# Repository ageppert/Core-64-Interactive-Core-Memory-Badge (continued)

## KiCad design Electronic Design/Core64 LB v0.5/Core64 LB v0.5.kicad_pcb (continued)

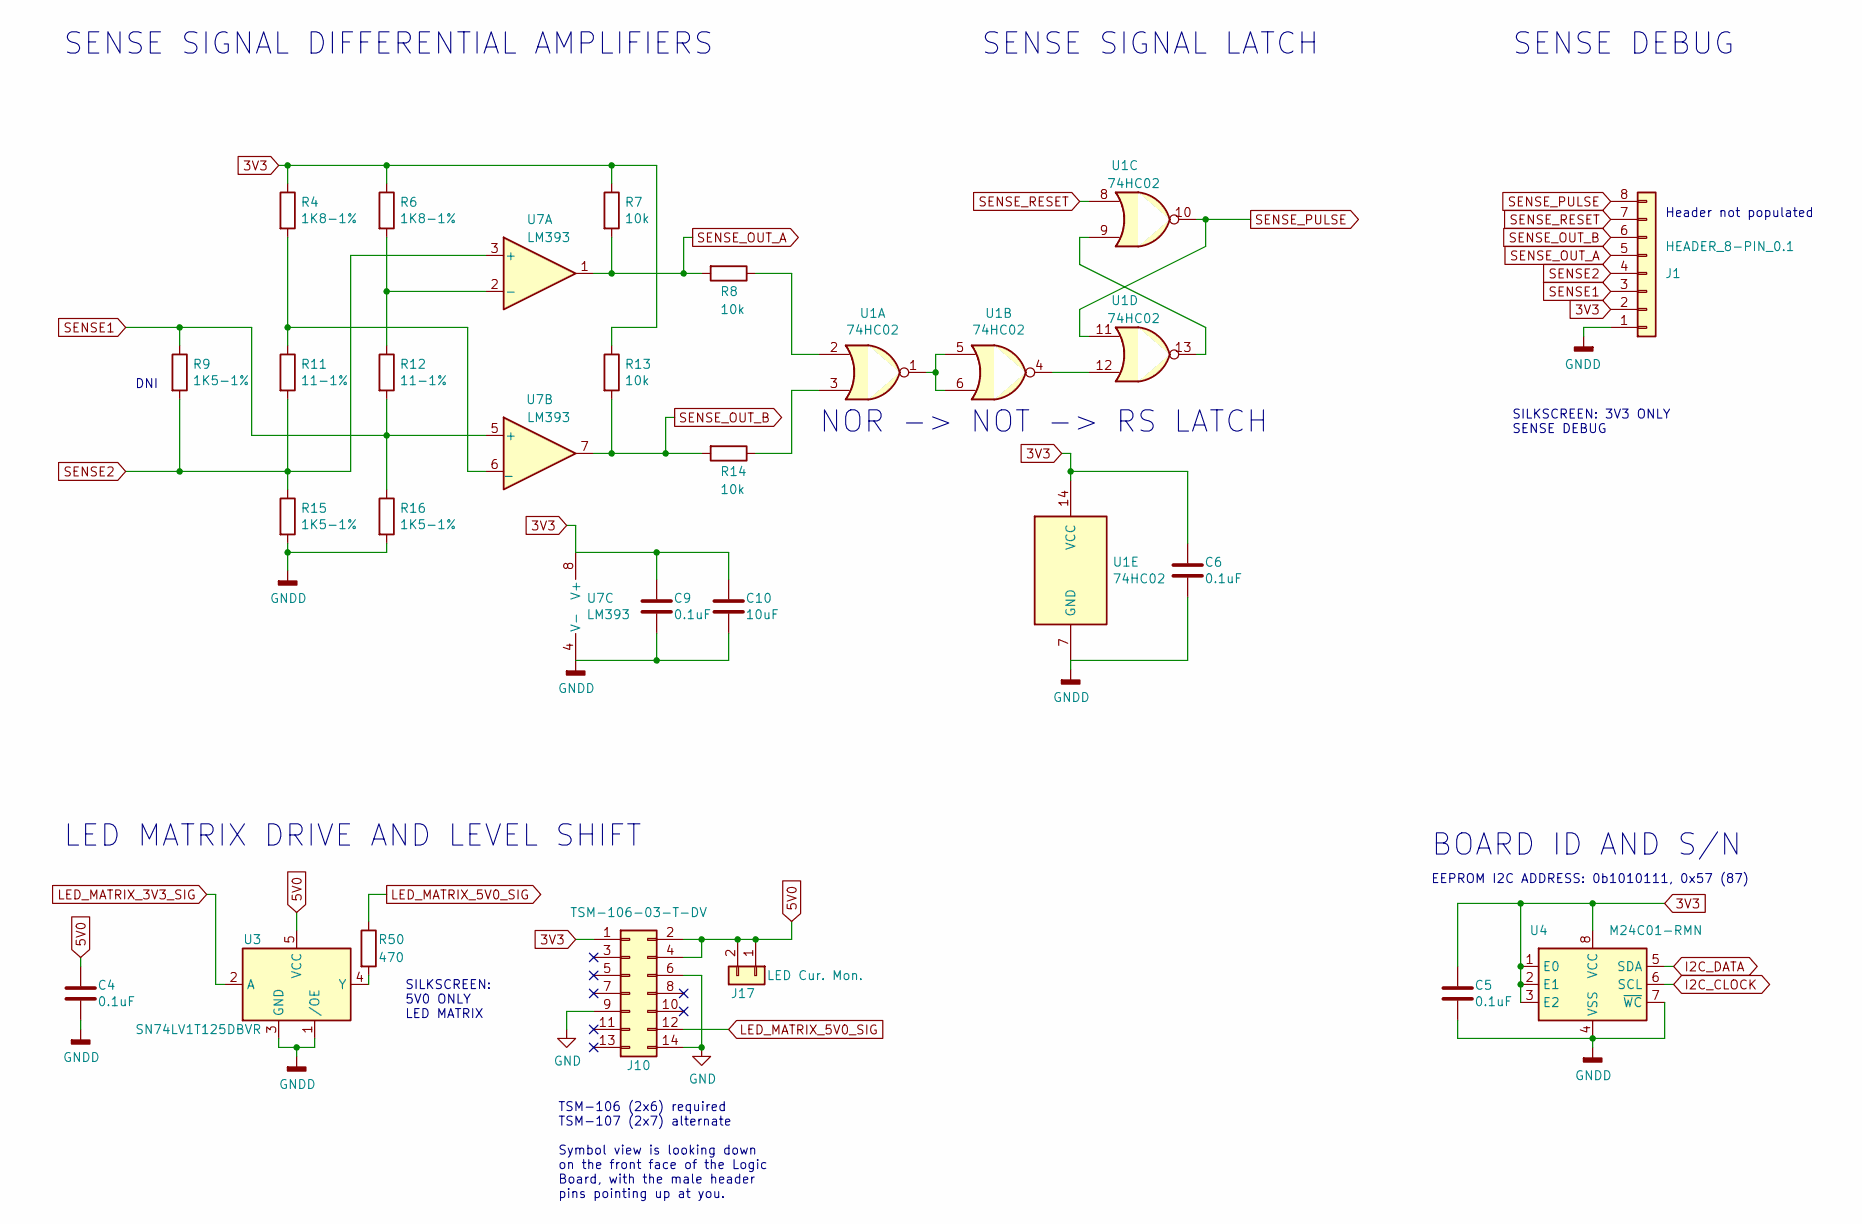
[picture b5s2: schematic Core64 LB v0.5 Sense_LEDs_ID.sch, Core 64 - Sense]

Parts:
C4, C5, C6, C9: 0.1uF; C_0805_2012Metric
C10: 10uF; C_0805_2012Metric
J1: HEADER_8-PIN_0.1; PinSocket_1x08_P2.54mm_Vertical
J10: TSM-106-03-T-DV‎; PinHeader_2x07_P2.54mm_Vertical_SMD_and_TH
J17: LED Cur. Mon.; PinSocket_1x02_P2.54mm_Vertical
R4, R6: 1K8-1%; R_0805_2012Metric
R7, R8, R13, R14: 10k; R_0805_2012Metric
R9, R15, R16: 1K5-1%; R_0805_2012Metric
R11, R12: 11-1%; R_0805_2012Metric
R50: 470; R_0805_2012Metric
U1: 74HC02; SOIC-14_3.9x8.7mm_P1.27mm
U3, U7: LM393; SOIC-8_W3.9mm
U4: M24C01-RMN; SOIC-8_3.9x4.9mm_P1.27mm

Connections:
3V3: C5.1, C6.1, C9.1, C10.1, J1.2, J10.1, R4.1, R6.1, R7.1, R13.1, U1.14 (VCC), U4.1 (E0), U4.2 (E1), U4.3 (E2), U4.8 (VCC), U7.8 (V+); also elsewhere on the board
5V0: C4.1, J10.2, J10.4, J17.1, J17.2, U3.5 (VCC); also elsewhere on the board
I2C_CLOCK: U4.6 (SCL); also elsewhere on the board
I2C_DATA: U4.5 (SDA); also elsewhere on the board
LED_MATRIX_5V0_SIG: J10.12, R50.1; also elsewhere on the board
unnamed: R8.1, U1.2
unnamed: R4.2, R11.1, U7.6 (_)
unnamed: R14.1, U1.3
unnamed: R50.2, U3.4 (Y)
unnamed: U1.1, U1.5, U1.6
unnamed: U1.4, U1.12
unnamed: U1.9, U1.13
SENSE1: J1.3, R9.1, R12.2, R16.1, U7.5 (+); also elsewhere on the board
SENSE_OUT_B: J1.6, R13.2, R14.2, U7.7
SENSE_PULSE: J1.8, U1.10, U1.11; also elsewhere on the board
SENSE_RESET: J1.7, U1.8; also elsewhere on the board

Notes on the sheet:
SENSE SIGNAL DIFFERENTIAL AMPLIFIERS
DNI
SENSE SIGNAL LATCH
SENSE DEBUG
SILKSCREEN: 3V3 ONLY SENSE DEBUG
NOR -> NOT -> RS LATCH
LED MATRIX DRIVE AND LEVEL SHIFT
TSM-106 (2x6) required TSM-107 (2x7) alternate Symbol view is looking down on the front face of the Logic Board, with the male header pins pointing up at you.
SILKSCREEN: 5V0 ONLY LED MATRIX
BOARD ID AND S/N
EEPROM I2C ADDRESS: 0b1010111, 0x57 (87)
Header not populated

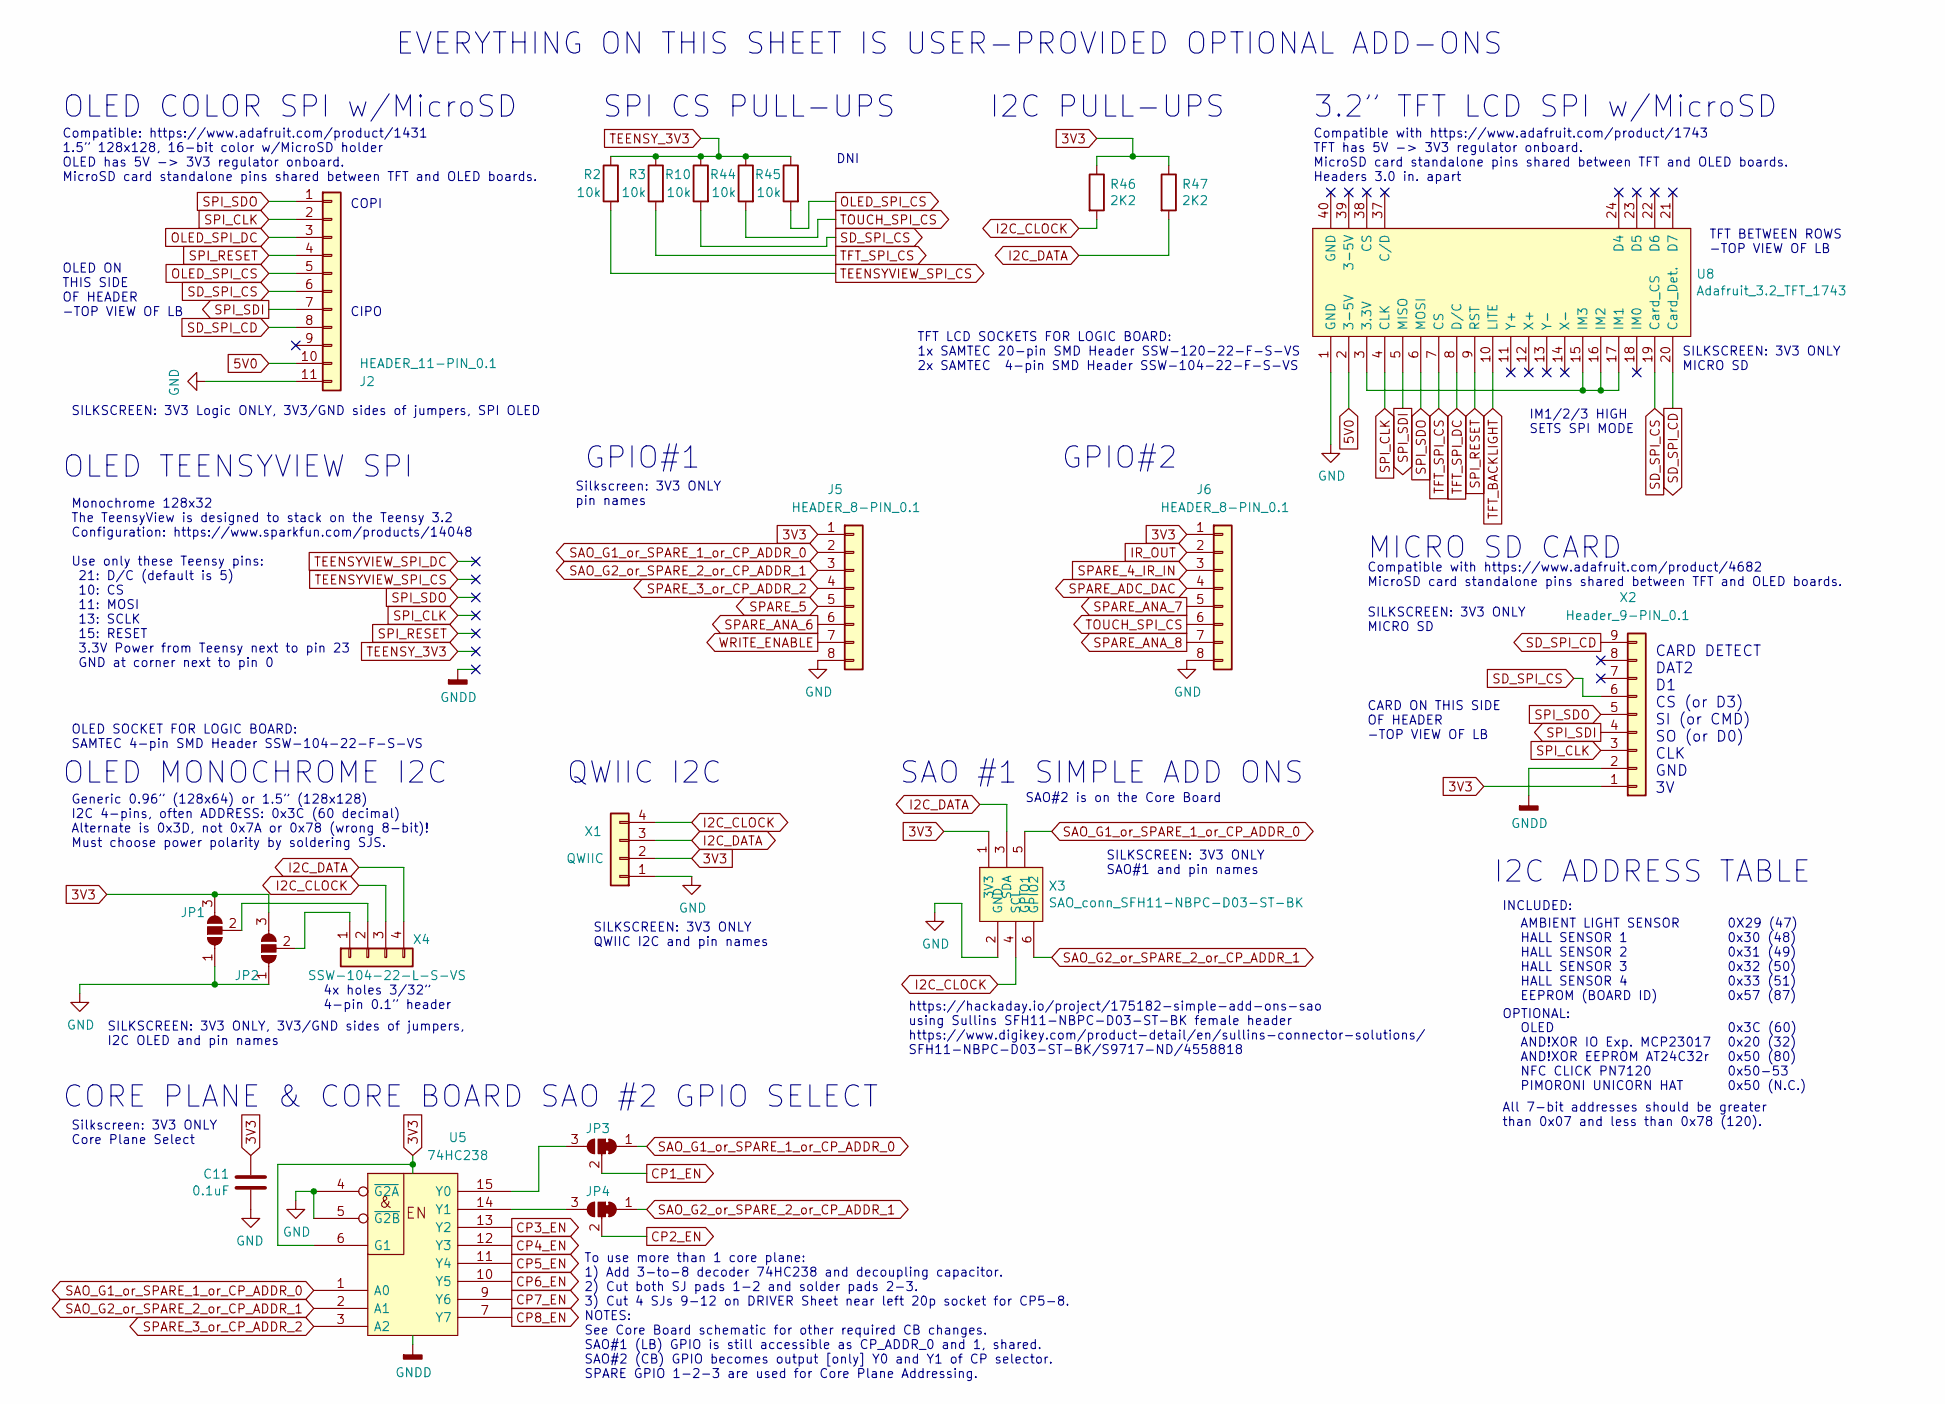
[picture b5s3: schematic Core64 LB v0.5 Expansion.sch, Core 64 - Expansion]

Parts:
C11: 0.1uF; C_0805_2012Metric
J2: HEADER_11-PIN_0.1; PinSocket_1x11_P2.54mm_Vertical
J5, J6: HEADER_8-PIN_0.1; PinSocket_1x08_P2.54mm_Vertical
JP1, JP2: SolderJumper_3_Open; SolderJumper-3_P1.3mm_Open_Pad1.0x1.5mm_NumberLabels
JP3, JP4: SolderJumper_3_Open; SolderJumper-3_P1.3mm_Bridged12_RoundedPad1.0x1.5mm_NumberL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
R2, R3, R10, R44, R45: 10k; R_0805_2012Metric
R46, R47: 2K2; R_0805_2012Metric
U5: 74HC238; TSSOP-16-W4.40mm
U8: Adafruit_3.2_TFT_1743; Adafruit_3.2_TFT_Dual_PinHeader_1x20_P2.54mm_Vertical_SMD_P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; Manufacturer_Part_Number MIKROE-971; Mouser Part Number 932-MIKROE-971
X1: QWIIC; JST_SH_SM04B-SRSS-TB_1x04-1MP_P1.00mm_Horizontal
X2: Header_9-PIN_0.1; PinSocket_1x09_P2.54mm_Vertical
X3: SAO_conn_SFH11-NBPC-D03-ST-BK; Badgelife-SAOv169-BADGE-2x3
X4: SSW-104-22-L-S-VS; PinSocket_1x04_P2.54mm_Vertical_SMD_and_TH_Pin1Left

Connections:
3V3: C11.1, J5.1, J6.1, JP1.3 (B), JP2.3 (B), R46.1, R47.1, U5.6 (G1), U5.16 (VCC), X1.2, X2.1, X3.1 (3V3); also elsewhere on the board
5V0: J2.10, U8.2 (3-5V); also elsewhere on the board
5V0_MON: J5.4, U5.3 (A2); also elsewhere on the board
CP1_EN: JP3.2 (C); also elsewhere on the board
CP2_EN: JP4.2 (C); also elsewhere on the board
CP3_EN: U5.13 (Y2); also elsewhere on the board
CP4_EN: U5.12 (Y3); also elsewhere on the board
CP5_EN: U5.11 (Y4); also elsewhere on the board
CP6_EN: U5.10 (Y5); also elsewhere on the board
CP7_EN: U5.9 (Y6); also elsewhere on the board
CP8_EN: U5.7 (Y7); also elsewhere on the board
HS1: J5.2, JP3.1 (A), U5.1 (A0), X3.5 (GPIO1); also elsewhere on the board
HS2: J5.3, JP4.1 (A), U5.2 (A1), X3.6 (GPIO2); also elsewhere on the board
HS4: J6.3, R2.2; also elsewhere on the board
I2C_CLOCK: R46.2, X1.4, X3.4 (SCL), X4.3; also elsewhere on the board
I2C_DATA: R47.2, X1.3, X3.3 (SDA), X4.4; also elsewhere on the board
IR_OUT: J6.2; also elsewhere on the board
unnamed: JP1.2 (C), X4.2
unnamed: JP2.2 (C), X4.1
unnamed: JP3.3 (B), U5.15 (Y0)
unnamed: JP4.3 (B), U5.14 (Y1)
unnamed: U8.3 (3.3V), U8.15 (IM3), U8.16 (IM2), U8.17 (IM1)
OLED_SPI_CS: J2.5, R45.2; also elsewhere on the board
OLED_SPI_DC: J2.3, J5.7; also elsewhere on the board
Q2P: J6.6, R44.2; also elsewhere on the board
Q3P: J2.6, R10.2, U8.19 (Card_CS), X2.6; also elsewhere on the board
Q4N: U8.8 (D/C); also elsewhere on the board
Q4P: R3.2, U8.7 (CS); also elsewhere on the board
SD_SPI_CD: J2.8, U8.20 (Card_Det.), X2.9; also elsewhere on the board
SPARE_5: J2.4, J5.5, U8.9 (RST); also elsewhere on the board
SPARE_ADC_DAC: J6.4; also elsewhere on the board
SPARE_ANA_6: J5.6; also elsewhere on the board
SPARE_ANA_7: J6.5; also elsewhere on the board
SPARE_ANA_8: J6.7; also elsewhere on the board
SPI_CLK: J2.2, U8.4 (CLK), X2.3; also elsewhere on the board
SPI_SDI: J2.7, U8.5 (MISO), X2.4; also elsewhere on the board
SPI_SDO: J2.1, U8.6 (MOSI), X2.5; also elsewhere on the board
TEENSY_3V3: R2.1, R3.1, R10.1, R44.1, R45.1; also elsewhere on the board

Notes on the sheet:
CORE PLANE & CORE BOARD SAO #2 GPIO SELECT
SAO #1 SIMPLE ADD ONS
OLED MONOCHROME I2C
Generic 0.96” (128x64) or 1.5” (128x128) I2C 4-pins, often ADDRESS: 0x3C (60 decimal) Alternate is 0x3D, not 0x7A or 0x78 (wrong 8-bit)! Must choose power polarity by soldering SJS.
https://hackaday.io/project/175182-simple-add-ons-sao using Sullins SFH11-NBPC-D03-ST-BK female header https://www.digikey.com/product-detail/en/sullins-connector-solutions/ SFH11-NBPC-D03-ST-BK/S9717-ND/4558818
QWIIC I2C
MICRO SD CARD
Compatible with https://www.adafruit.com/product/4682 MicroSD card standalone pins shared between TFT and OLED boards.
SILKSCREEN: 3V3 ONLY, 3V3/GND sides of jumpers, I2C OLED and pin names
SILKSCREEN: 3V3 ONLY SAO#1 and pin names
Silkscreen: 3V3 ONLY pin names
OLED COLOR SPI w/MicroSD
3.2” TFT LCD SPI w/MicroSD
GPIO#1
EVERYTHING ON THIS SHEET IS USER-PROVIDED OPTIONAL ADD-ONS
To use more than 1 core plane: 1) Add 3-to-8 decoder 74HC238 and decoupling capacitor. 2) Cut both SJ pads 1-2 and solder pads 2-3. 3) Cut 4 SJs 9-12 on DRIVER Sheet near left 20p socket for CP5-8. NOTES: See Core Board schematic for other required CB changes. SAO#1 (LB) GPIO is still accessible as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
Silkscreen: 3V3 ONLY Core Plane Select
4x holes 3/32” 4-pin 0.1” header
SILKSCREEN: 3V3 ONLY QWIIC I2C and pin names
SILKSCREEN: 3V3 Logic ONLY, 3V3/GND sides of jumpers, SPI OLED
SILKSCREEN: 3V3 ONLY MICRO SD
SAO#2 is on the Core Board
CARD ON THIS SIDE OF HEADER -TOP VIEW OF LB
GPIO#2
Compatible with https://www.adafruit.com/product/1743 TFT has 5V -> 3V3 regulator onboard. MicroSD card standalone pins shared between TFT and OLED boards. Headers 3.0 in. apart
All 7-bit addresses should be greater than 0x07 and less than 0x78 (120).
AMBIENT LIGHT SENSOR HALL SENSOR 1 HALL SENSOR 2 HALL SENSOR 3 HALL SENSOR 4 EEPROM (BOARD ID)
0X29 (47) 0x30 (48) 0x31 (49) 0x32 (50) 0x33 (51) 0x57 (87)
INCLUDED:
OPTIONAL:
OLED AND!XOR IO Exp. MCP23017 AND!XOR EEPROM AT24C32r NFC CLICK PN7120 PIMORONI UNICORN HAT
0x3C (60) 0x20 (32) 0x50 (80) 0x50-53 0x50 (N.C.)
I2C ADDRESS TABLE
OLED TEENSYVIEW SPI
Monochrome 128x32 The TeensyView is designed to stack on the Teensy 3.2 Configuration: https://www.sparkfun.com/products/14048 Use only these Teensy pins: 21: D/C (default is 5) 10: CS 11: MOSI 13: SCLK 15: RESET 3.3V Power from Teensy next to pin 23 GND at corner next to pin 0
Compatible: https://www.adafruit.com/product/1431 1.5” 128x128, 16-bit color w/MicroSD holder OLED has 5V -> 3V3 regulator onboard. MicroSD card standalone pins shared between TFT and OLED boards.
OLED ON THIS SIDE OF HEADER -TOP VIEW OF LB
I2C PULL-UPS
SPI CS PULL-UPS
DNI

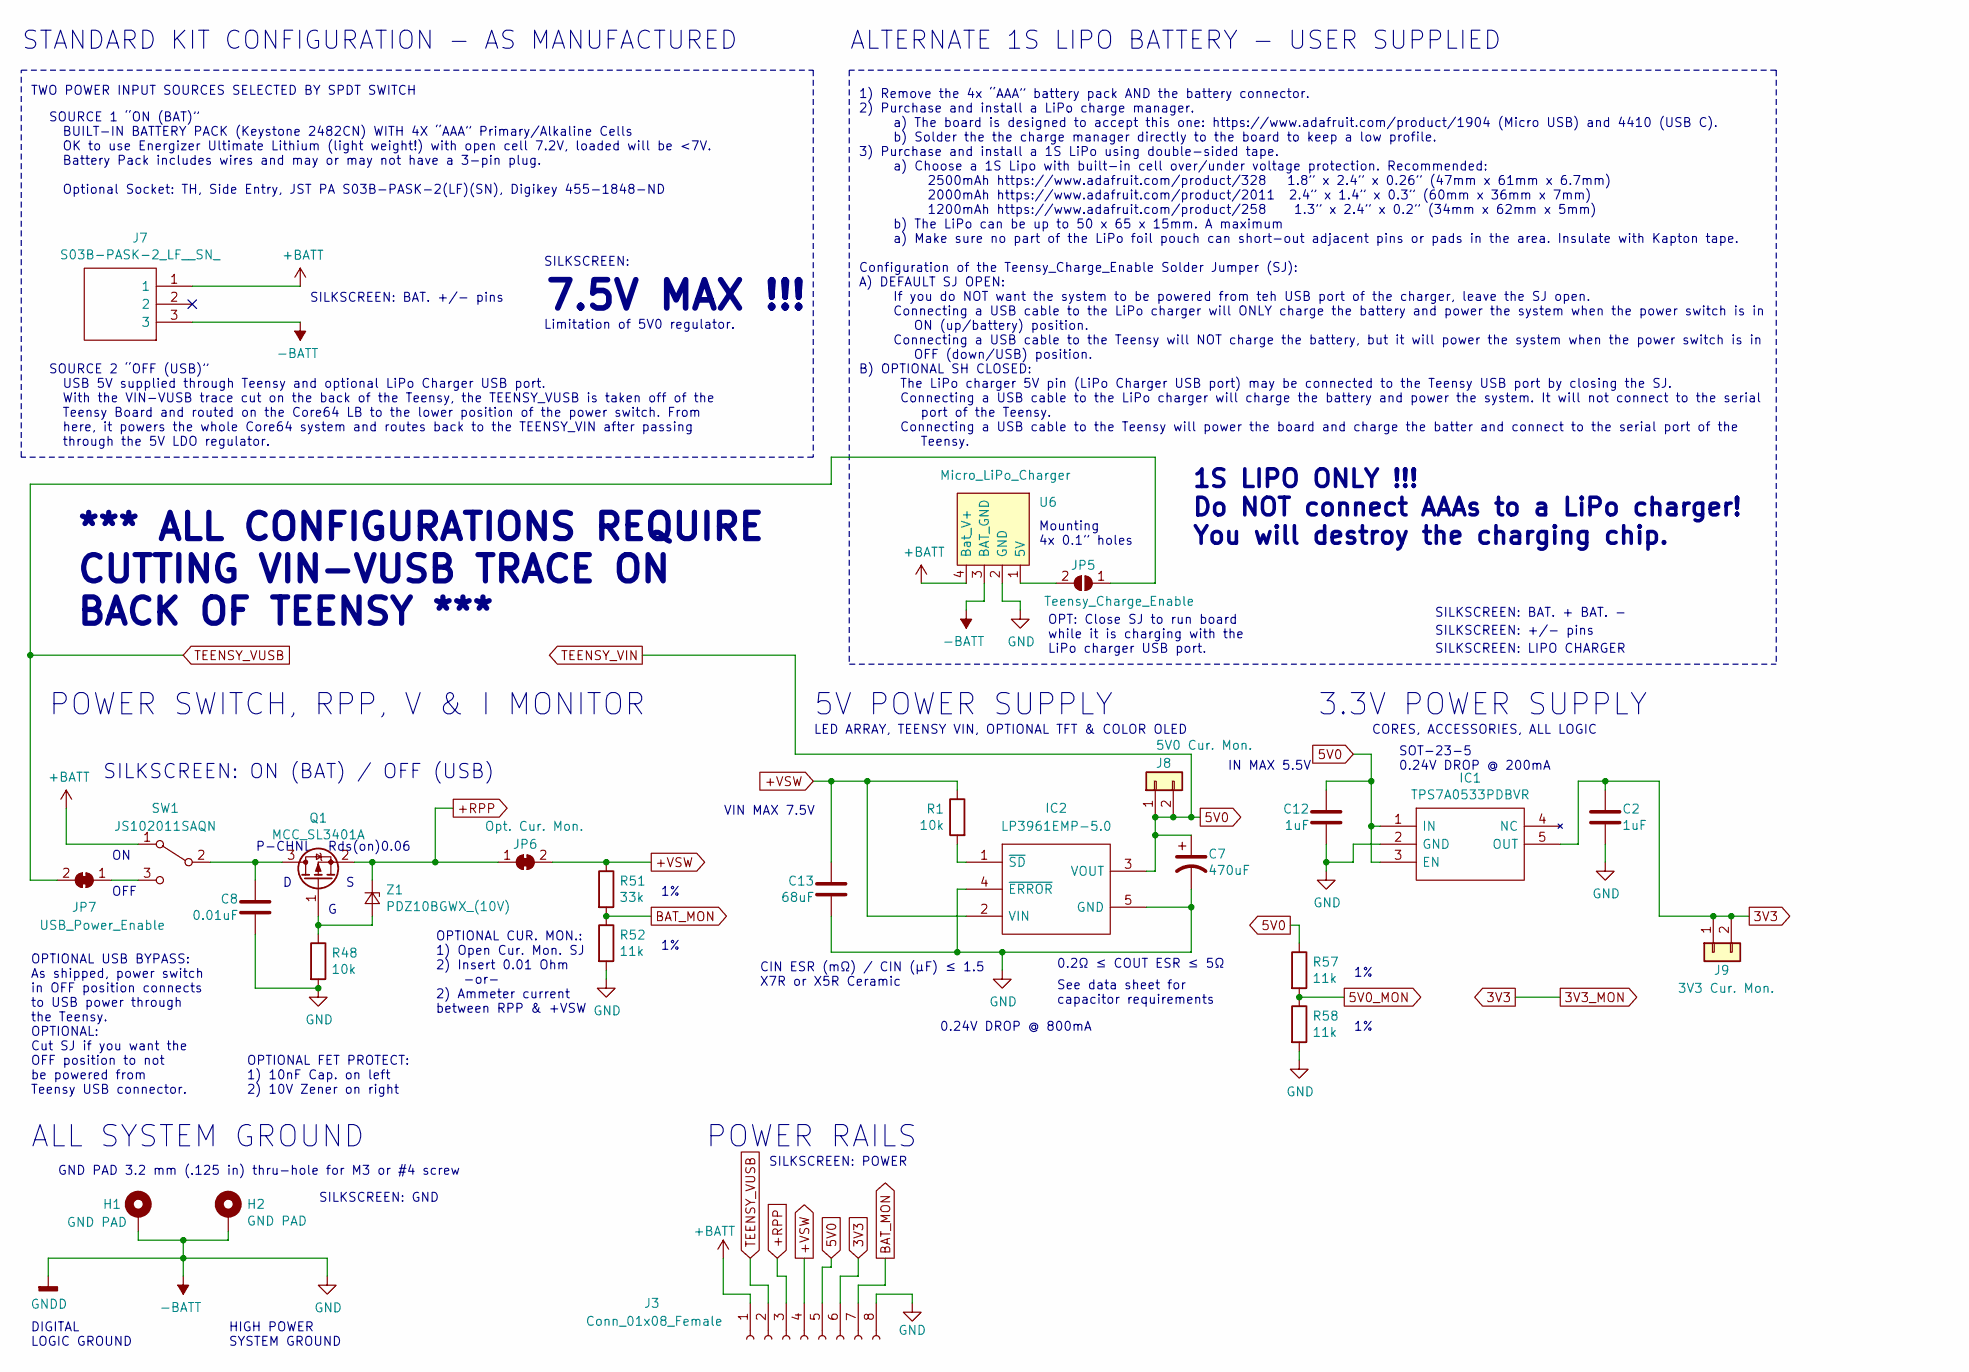
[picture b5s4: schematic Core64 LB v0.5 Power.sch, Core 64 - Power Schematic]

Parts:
C2, C12: 1uF; C_0805_2012Metric
C7: 470uF; CP_Elec_6.3x7.7; Digikey 565-EMHL100ARA471MHA0GCT-ND
C8: 0.01uF; C_0805_2012Metric
C13: 68uF; C_1206_3216Metric
H1, H2: GND PAD; MountingHole_3.2mm_M3_Pad_Via
IC1: TPS7A0533PDBVR; SOT95P280X145-5N; Manufacturer_Part_Number TPS7A0533PDBVR; Mouser Part Number 595-TPS7A0533PDBVR
IC2: LP3961EMP-5.0; SOT150P696X180-5N; Manufacturer_Part_Number LP3961EMP-5.0; Mouser Part Number 926-LP3961EMP-50
J3: Conn_01x08_Female; PinSocket_1x08_P2.54mm_Vertical
J7: S03B-PASK-2_LF__SN_; S03BPASK2LFSN_.075in_holes; Manufacturer_Part_Number S03B-PASK-2(LF)(SN)
J8: 5V0 Cur. Mon.; PinSocket_1x02_P2.54mm_Vertical
J9: 3V3 Cur. Mon.; PinSocket_1x02_P2.54mm_Vertical
JP5: Teensy_Charge_Enable; SolderJumper-2_P1.3mm_Open_RoundedPad1.0x1.5mm
JP6: Opt. Cur. Mon.; SolderJumper-2_P1.3mm_Bridged_Pad1.0x1.5mm
JP7: USB_Power_Enable; SolderJumper-2_P1.3mm_Bridged_Pad1.0x1.5mm
Q1: MCC_SL3401A; SOT-23-3
R1, R48: 10k; R_0805_2012Metric
R51: 33k; R_0805_2012Metric
R52, R57, R58: 11k; R_0805_2012Metric
SW1: JS102011SAQN; SW_SPDT_CK-JS102011SAQN_Core64_Recessed
U6: Micro_LiPo_Charger; Micro_LiPo_Charger_CornerSMD
Z1: PDZ10BGWX_(10V); SOD-123

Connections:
3V3: C2.1, IC1.5 (OUT), J3.6, J9.1, J9.2; also elsewhere on the board
5V0: C7.1, C12.1, IC1.1 (IN), IC1.3 (EN), IC2.3 (VOUT), J3.5, J8.1, J8.2, R57.1; also elsewhere on the board
5V0_MON: R57.2, R58.1; also elsewhere on the board
+BATT: J3.1, J7.1, SW1.1 (A), U6.4 (Bat_V+); also elsewhere on the board
+RPP: J3.3, JP6.1 (A), Q1.2 (S), Z1.1 (K)
+VSW: C13.1, IC2.2 (VIN), J3.4, JP6.2 (B), R1.1, R51.1
BAT_MON: J3.7, R51.2, R52.1; also elsewhere on the board
unnamed: C8.1, Q1.3 (D), SW1.2 (B)
unnamed: IC2.1 (~SD), R1.2
unnamed: JP5.2 (B), U6.1 (5V)
unnamed: JP7.1 (A), SW1.3 (C)
unnamed: Q1.1 (G), R48.1, Z1.2 (A)
TEENSY_VUSB: J3.2, JP5.1 (A), JP7.2 (B); also elsewhere on the board

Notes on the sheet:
CORES, ACCESSORIES, ALL LOGIC
SOURCE 1 “ON (BAT)” BUILT-IN BATTERY PACK (Keystone 2482CN) WITH 4X “AAA” Primary/Alkaline Cells OK to use Energizer Ultimate Lithium (light weight!) with open cell 7.2V, loaded will be <7V. Battery Pack includes wires and may or may not have a 3-pin plug. Optional Socket: TH, Side Entry, JST PA S0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
SOURCE 2 “OFF (USB)” USB 5V supplied through Teensy and optional LiPo Charger USB port. With the VIN-VUSB trace cut on the back of the Teensy, the TEENSY_VUSB is taken off of the Teensy Board and routed on the Core64 LB to the lower position of the power switch. From here, it powers the whole Core6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
TWO POWER INPUT SOURCES SELECTED BY SPDT SWITCH
STANDARD KIT CONFIGURATION - AS MANUFACTURED
ALTERNATE 1S LIPO BATTERY - USER SUPPLIED
POWER SWITCH, RPP, V & I MONITOR
3.3V POWER SUPPLY
LED ARRAY, TEENSY VIN, OPTIONAL TFT & COLOR OLED
ALL SYSTEM GROUND
POWER RAILS
HIGH POWER SYSTEM GROUND
DIGITAL LOGIC GROUND
OPTIONAL USB BYPASS: As shipped, power switch in OFF position connects to USB power through the Teensy. OPTIONAL: Cut SJ if you want the OFF position to not be powered from Teensy USB connector.
SILKSCREEN: ON (BAT) / OFF (USB)
7.5V MAX !!!
SILKSCREEN: BAT. +/- pins
OPTIONAL CUR. MON.: 1) Open Cur. Mon. SJ 2) Insert 0.01 Ohm -or- 2) Ammeter current between RPP & +VSW
5V POWER SUPPLY
P-CHNL
*** ALL CONFIGURATIONS REQUIRE CUTTING VIN-VUSB TRACE ON BACK OF TEENSY ***
1S LIPO ONLY !!! Do NOT connect AAAs to a LiPo charger! You will destroy the charging chip.
OPTIONAL FET PROTECT: 1) 10nF Cap. on left 2) 10V Zener on right
SILKSCREEN: +/- pins
1) Remove the 4x “AAA” battery pack AND the battery connector. 2) Purchase and install a LiPo charge manager. a) The board is designed to accept this one: https://www.adafruit.com/product/1904 (Micro USB) and 4410 (USB C). b) Solder the the charge manager directly to the board to keep a low profile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
OPT: Close SJ to run board while it is charging with the LiPo charger USB port.
SOT-23-5 0.24V DROP @ 200mA
CIN ESR (mΩ) / CIN (μF) ≤ 1.5 X7R or X5R Ceramic
0.2Ω ≤ COUT ESR ≤ 5Ω
See data sheet for capacitor requirements
GND PAD 3.2 mm (.125 in) thru-hole for M3 or #4 screw
SILKSCREEN: GND
SILKSCREEN: LIPO CHARGER
SILKSCREEN: BAT. + BAT. -
SILKSCREEN: POWER
Mounting 4x 0.1” holes
SILKSCREEN:
Limitation of 5V0 regulator.
OFF
Rds(on)0.06

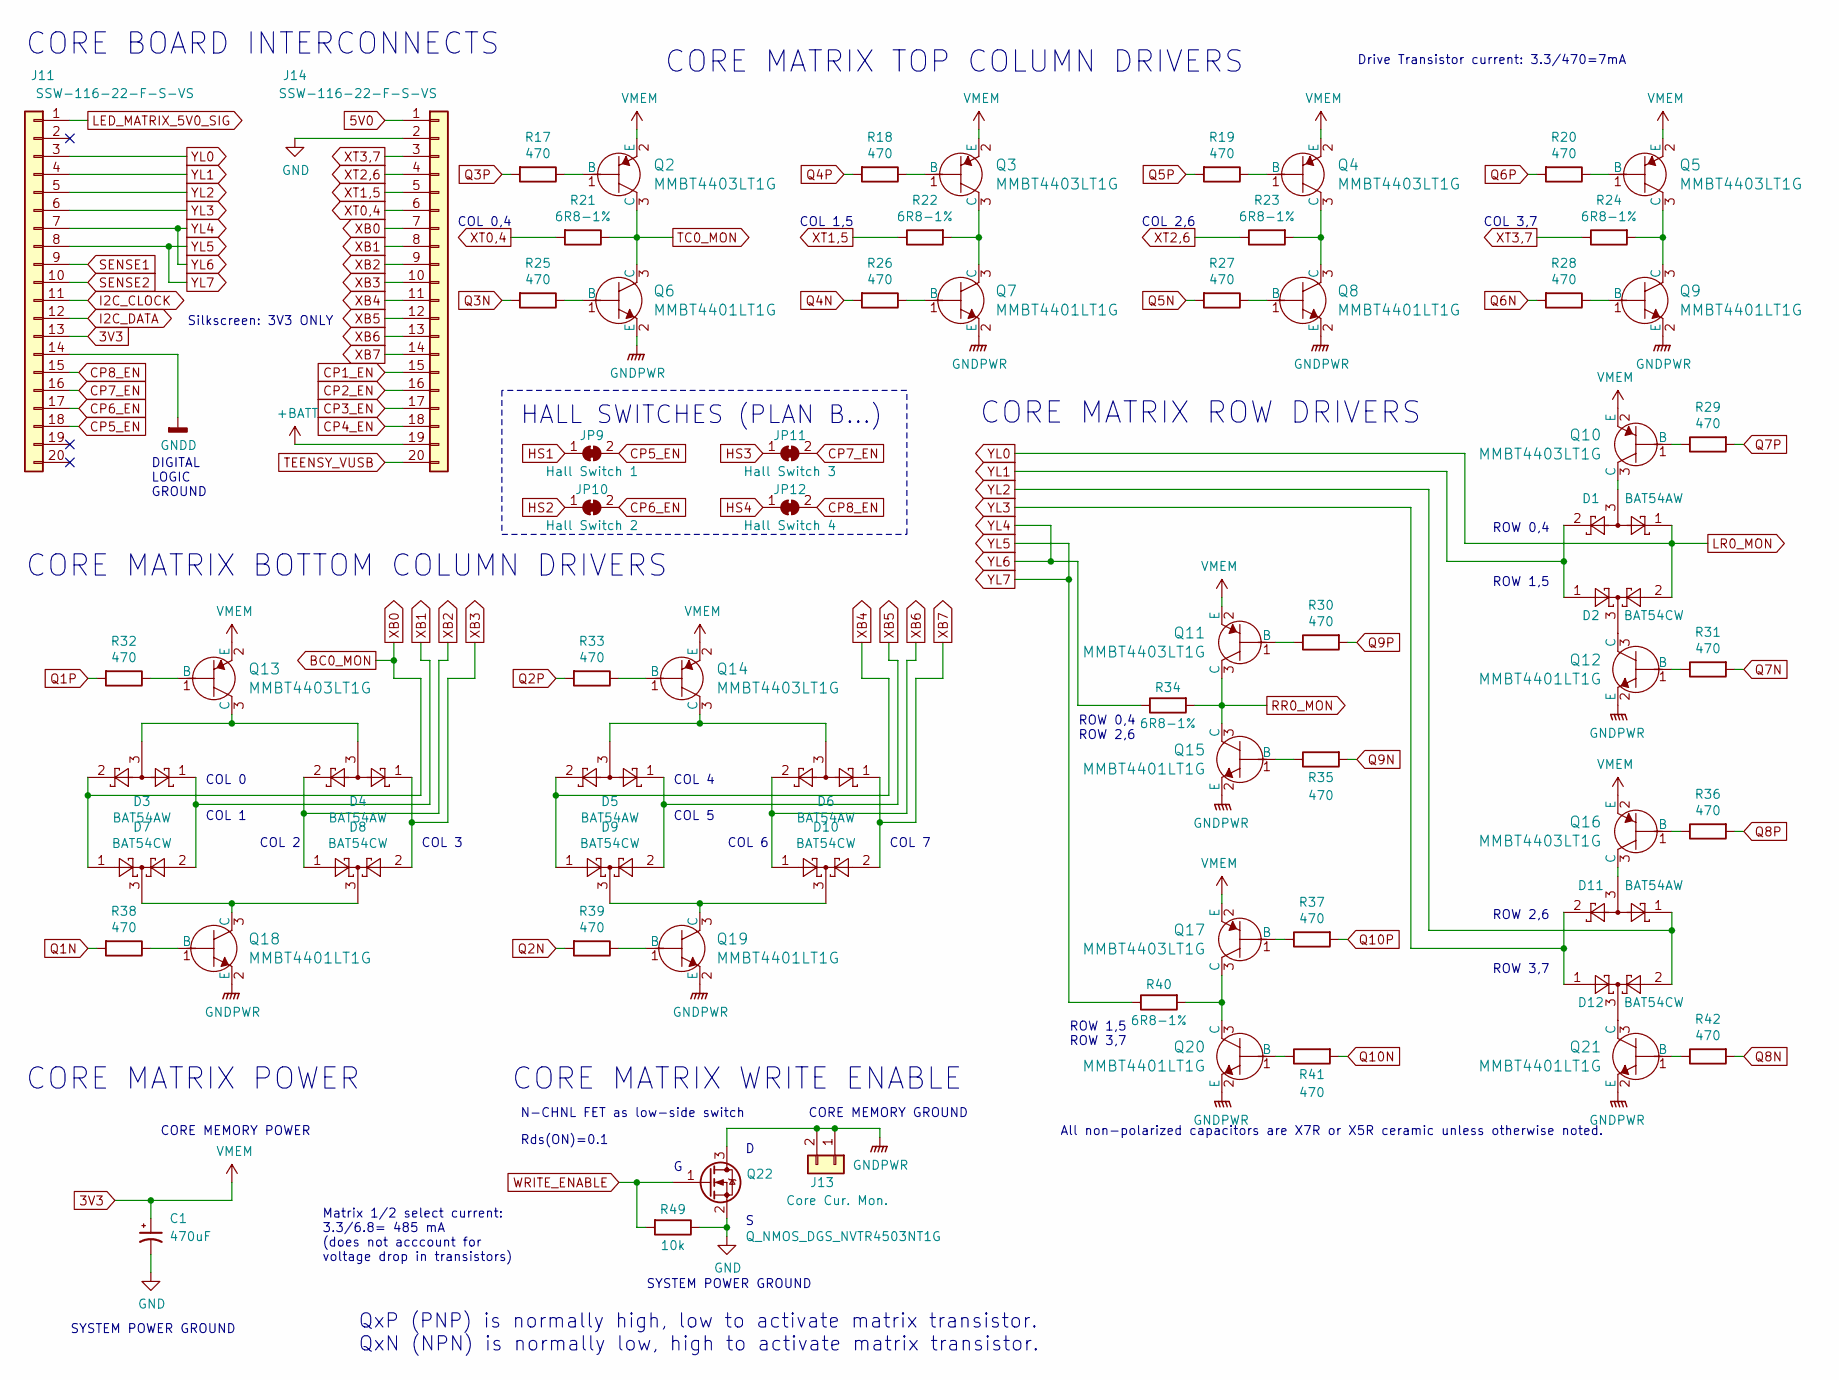
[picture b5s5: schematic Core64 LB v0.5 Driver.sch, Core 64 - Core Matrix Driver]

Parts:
C1: 470uF; CP_Elec_6.3x7.7; Digikey 565-EMHL100ARA471MHA0GCT-ND
D1, D3, D4, D5, D6, D11: BAT54AW; SOT-323_SC-70
D2, D7, D8, D9, D10, D12: BAT54CW; SOT-323_SC-70
J11, J14: SSW-116-22-F-S-VS‎; PinHeader_1x20_P2.54mm_Vertical
J13: Core Cur. Mon.; PinSocket_1x02_P2.54mm_Vertical
JP9: Hall Switch 1; SolderJumper-2_P1.3mm_Bridged_RoundedPad1.0x1.5mm
JP10: Hall Switch 2; SolderJumper-2_P1.3mm_Bridged_RoundedPad1.0x1.5mm
JP11: Hall Switch 3; SolderJumper-2_P1.3mm_Bridged_RoundedPad1.0x1.5mm
JP12: Hall Switch 4; SolderJumper-2_P1.3mm_Bridged_RoundedPad1.0x1.5mm
Q2, Q3, Q4, Q5, Q10, Q11, Q13, Q14, Q16, Q17: MMBT4403LT1G; SOT-23-3; MPN MMBT4403LT1G; Digi-Key_PN MMBT4403LT1GOSCT-ND
Q6, Q7, Q8, Q9, Q12, Q15, Q18, Q19, Q20, Q21: MMBT4401LT1G; SOT-23-3; MPN MMBT4401LT1G; Digi-Key_PN MMBT4401LT1GOSCT-ND
Q22: Q_NMOS_DGS_NVTR4503NT1G; SOT-23-3
R17, R18, R19, R20, R25, R26, R27, R28, R29, R30, R31, R32, R33, R35, R36, R37, R38, R39, R41, R42: 470; R_0805_2012Metric
R21, R22, R23, R24, R34, R40: 6R8-1%; R_0805_2012Metric
R49: 10k; R_0805_2012Metric

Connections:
3V3: C1.1, J11.13, Q2.2 (E), Q3.2 (E), Q4.2 (E), Q5.2 (E), Q10.2 (E), Q11.2 (E), Q13.2 (E), Q14.2 (E), Q16.2 (E), Q17.2 (E); also elsewhere on the board
5V0: J14.1; also elsewhere on the board
5V0_MON: JP11.1 (A); also elsewhere on the board
+BATT: J14.19; also elsewhere on the board
BC0_MON: D3.2, D7.1, J14.7; also elsewhere on the board
CP1_EN: J14.15; also elsewhere on the board
CP2_EN: J14.16; also elsewhere on the board
CP3_EN: J14.17; also elsewhere on the board
CP4_EN: J14.18; also elsewhere on the board
CP5_EN: J11.18, JP9.2 (B); also elsewhere on the board
CP6_EN: J11.17, JP10.2 (B); also elsewhere on the board
CP7_EN: J11.16, JP11.2 (B); also elsewhere on the board
CP8_EN: J11.15, JP12.2 (B); also elsewhere on the board
GNDPWR: J13.1, J13.2, Q6.2 (E), Q7.2 (E), Q8.2 (E), Q9.2 (E), Q12.2 (E), Q15.2 (E), Q18.2 (E), Q19.2 (E), Q20.2 (E), Q21.2 (E), Q22.3 (D)
HS1: JP9.1 (A); also elsewhere on the board
HS2: JP10.1 (A); also elsewhere on the board
HS4: JP12.1 (A); also elsewhere on the board
I2C_CLOCK: J11.11; also elsewhere on the board
I2C_DATA: J11.12; also elsewhere on the board
IR_OUT: R39.2; also elsewhere on the board
LED_MATRIX_5V0_SIG: J11.1; also elsewhere on the board
LR0_MON: D1.1, D2.2, J11.3; also elsewhere on the board
unnamed: D1.3, Q10.3 (C)
unnamed: D2.3, Q12.3 (C)
unnamed: D3.3, D4.3, Q13.3 (C)
unnamed: D5.3, D6.3, Q14.3 (C)
unnamed: D7.3, D8.3, Q18.3 (C)
unnamed: D9.3, D10.3, Q19.3 (C)
unnamed: D11.3, Q16.3 (C)
unnamed: D12.3, Q21.3 (C)
unnamed: Q2.1 (B), R17.1
unnamed: Q3.1 (B), R18.1
unnamed: Q3.3 (C), Q7.3 (C), R22.2
unnamed: Q4.1 (B), R19.1
unnamed: Q4.3 (C), Q8.3 (C), R23.2
unnamed: Q5.1 (B), R20.1
unnamed: Q5.3 (C), Q9.3 (C), R24.2
unnamed: Q6.1 (B), R25.1
unnamed: Q7.1 (B), R26.1
unnamed: Q8.1 (B), R27.1
unnamed: Q9.1 (B), R28.1
unnamed: Q10.1 (B), R29.1
unnamed: Q11.1 (B), R30.1
unnamed: Q12.1 (B), R31.1
unnamed: Q13.1 (B), R32.1
unnamed: Q14.1 (B), R33.1
unnamed: Q15.1 (B), R35.1
unnamed: Q16.1 (B), R36.1
unnamed: Q17.1 (B), R37.1
unnamed: Q17.3 (C), Q20.3 (C), R40.2
unnamed: Q18.1 (B), R38.1
unnamed: Q19.1 (B), R39.1
unnamed: Q20.1 (B), R41.1
unnamed: Q21.1 (B), R42.1
OLED_SPI_CS: R32.2; also elsewhere on the board
OLED_SPI_DC: Q22.1 (G), R49.2; also elsewhere on the board
Q1N: R38.2; also elsewhere on the board
Q2P: R33.2; also elsewhere on the board
Q3N: R25.2; also elsewhere on the board
Q3P: R17.2; also elsewhere on the board
Q4N: R26.2; also elsewhere on the board
Q4P: R18.2; also elsewhere on the board
Q5N: R27.2; also elsewhere on the board
Q5P: R19.2; also elsewhere on the board
Q6N: R28.2; also elsewhere on the board
Q6P: R20.2; also elsewhere on the board
Q7N: R31.2; also elsewhere on the board
Q7P: R29.2; also elsewhere on the board
Q8N: R42.2; also elsewhere on the board
Q8P: R36.2; also elsewhere on the board
Q9N: R35.2; also elsewhere on the board
Q9P: R30.2; also elsewhere on the board
Q10N: R41.2; also elsewhere on the board
Q10P: R37.2; also elsewhere on the board
RR0_MON: Q11.3 (C), Q15.3 (C), R34.2; also elsewhere on the board
SENSE1: J11.9; also elsewhere on the board
TC0_MON: Q2.3 (C), Q6.3 (C), R21.1; also elsewhere on the board
TEENSY_VUSB: J14.20; also elsewhere on the board
XB1: D3.1, D7.2, J14.8
XB2: D4.2, D8.1, J14.9
XB3: D4.1, D8.2, J14.10
XB4: D5.2, D9.1, J14.11
XB5: D5.1, D9.2, J14.12
XB6: D6.2, D10.1, J14.13
XB7: D6.1, D10.2, J14.14
XT0,4: J14.6, R21.2
XT1,5: J14.5, R22.1
XT2,6: J14.4, R23.1
XT3,7: J14.3, R24.1
YL1: D1.2, D2.1, J11.4
YL2: D11.1, D12.2, J11.5
YL3: D11.2, D12.1, J11.6
YL4: J11.7, R34.1
YL5: J11.8, R40.1

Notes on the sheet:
Matrix 1/2 select current: 3.3/6.8= 485 mA (does not acccount for voltage drop in transistors)
COL 0,4
COL 1,5
COL 2,6
COL 3,7
COL 0
COL 1
COL 2
COL 3
COL 4
COL 5
COL 6
COL 7
ROW 0,4 ROW 2,6
ROW 1,5 ROW 3,7
ROW 0,4
ROW 3,7
ROW 1,5
ROW 2,6
CORE MEMORY GROUND
CORE MEMORY POWER
CORE MATRIX POWER
CORE MATRIX BOTTOM COLUMN DRIVERS
CORE MATRIX TOP COLUMN DRIVERS
CORE MATRIX ROW DRIVERS
CORE MATRIX WRITE ENABLE
DIGITAL LOGIC GROUND
SYSTEM POWER GROUND
CORE BOARD INTERCONNECTS
All non-polarized capacitors are X7R or X5R ceramic unless otherwise noted.
Silkscreen: 3V3 ONLY
QxP (PNP) is normally high, low to activate matrix transistor. QxN (NPN) is normally low, high to activate matrix transistor.
N-CHNL FET as low-side switch
Rds(ON)=0.1
Drive Transistor current: 3.3/470=7mA
HALL SWITCHES (PLAN B…)

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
